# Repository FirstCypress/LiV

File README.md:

LiV is a sensor expansion board that turns your Raspberry Pi model B or B+ into a modern indoor air quality monitoring device that measures CO2, temperature, humidity and air pressure. 

LiV's software is released under a MIT license. 

LiV’s hardware is released under a cc-by-sa 4.0 license. 

LiV’s case is released under a cc-by-sa 4.0 license.

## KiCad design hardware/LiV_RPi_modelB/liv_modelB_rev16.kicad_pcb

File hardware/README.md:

LiV’s hardware is released under a cc-by-sa 4.0 license.

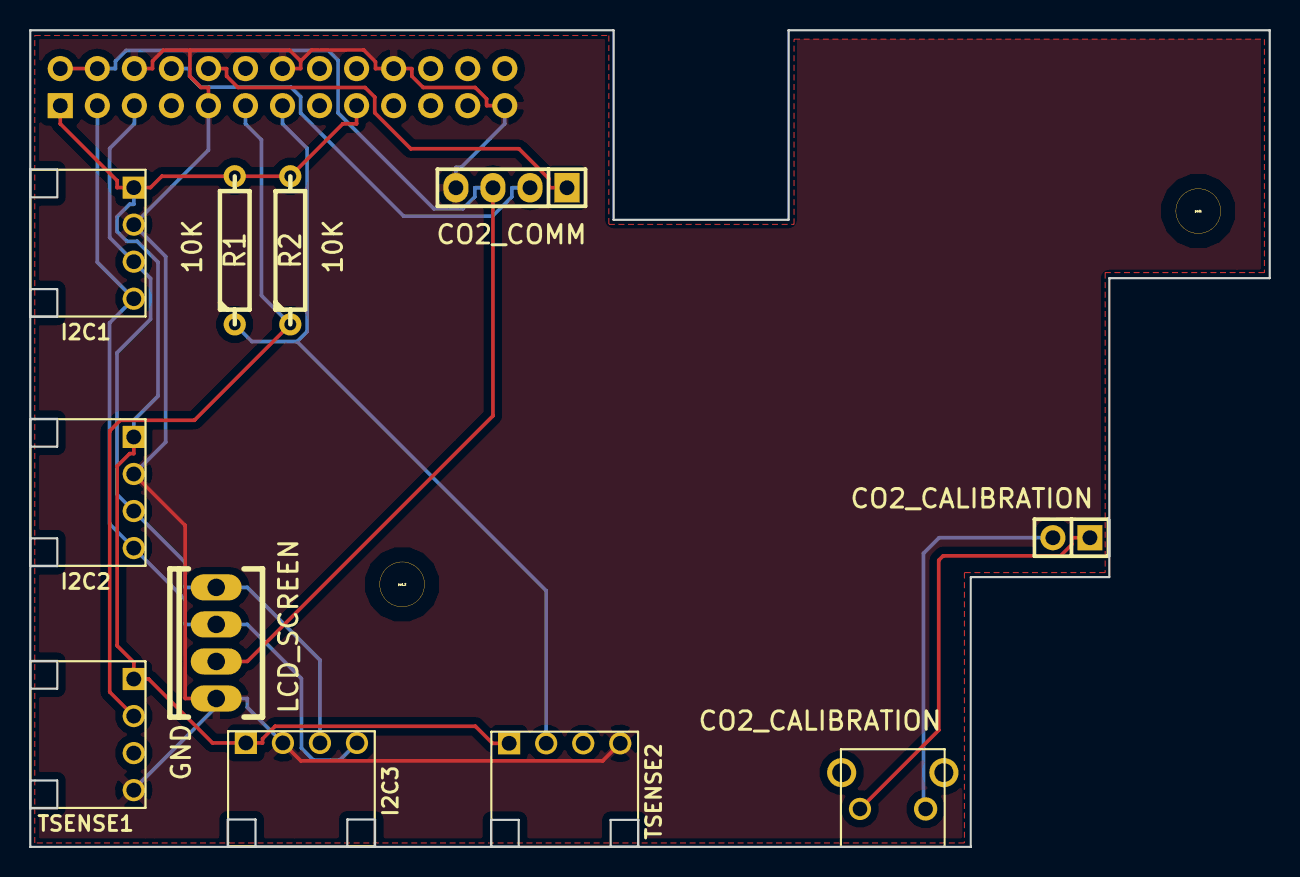
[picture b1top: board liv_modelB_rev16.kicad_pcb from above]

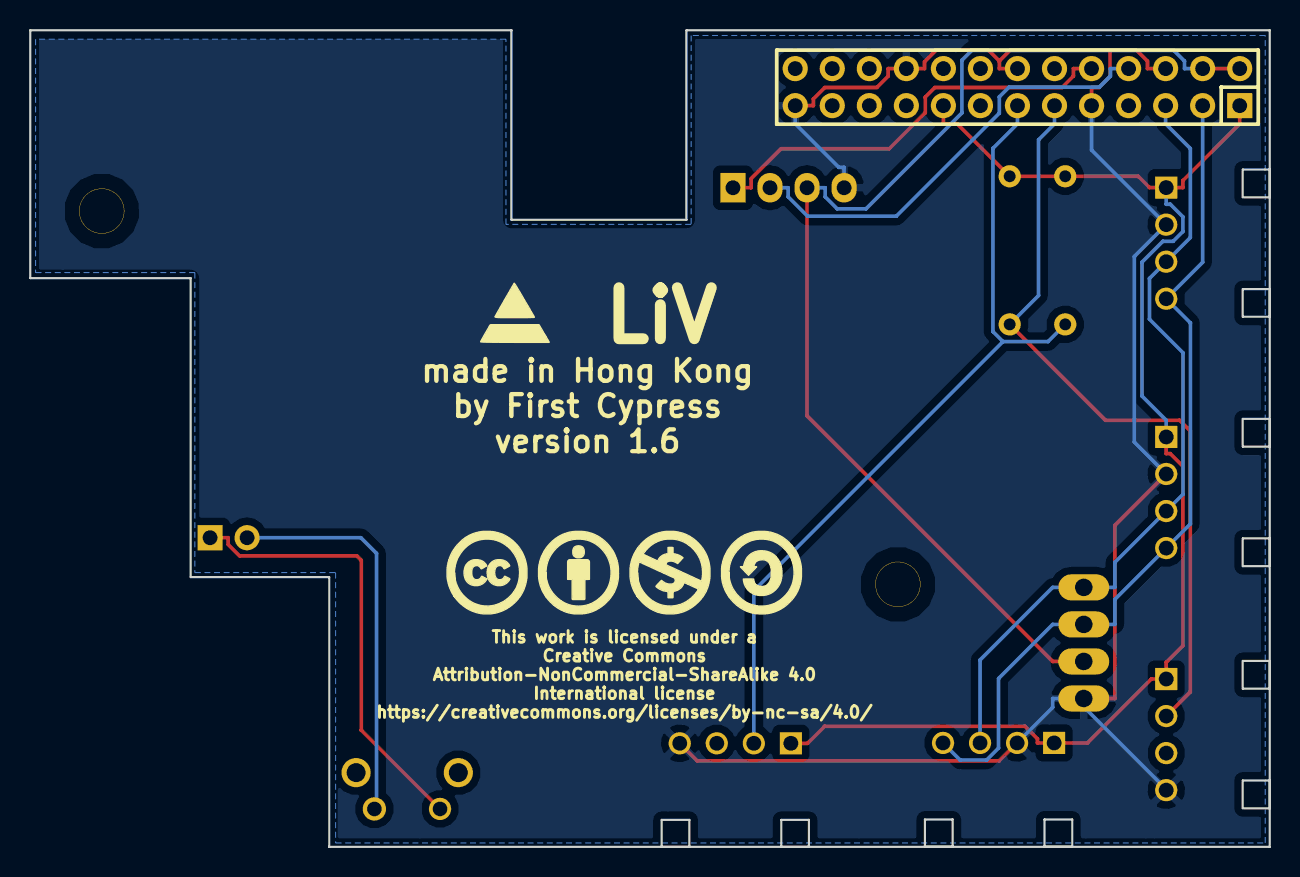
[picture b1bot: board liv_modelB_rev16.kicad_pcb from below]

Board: 2 copper layers, 85.0 x 56.0 mm, 15 parts (2 on the bottom side), 11 nets.

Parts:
P1: CONN_13X2; Socket_Strip_Straight_2x13
P3: LCD_SCREEN; Socket_MOLEX-KK-RM2-54mm_Lock_4pin_straight
P4: CO2_CALIBRATION; Socket_Strip_Straight_2x01
P5: CO2_COMM; Socket_Strip_Straight_1x04
P6: I2C1; CONNECTOR_MOLEX_4PIN_RIGHT_ANGLE
P7: I2C2; CONNECTOR_MOLEX_4PIN_RIGHT_ANGLE
P8: TSENSE2; CONNECTOR_MOLEX_4PIN_RIGHT_ANGLE
P9: TSENSE1; CONNECTOR_MOLEX_4PIN_RIGHT_ANGLE
P10: I2C3; CONNECTOR_MOLEX_4PIN_RIGHT_ANGLE
R1, R2: 10k; R4
SW1: CO2_CALIBRATION; SWITCH_TACT_RIGHT_ANGLE
cc_by_nc_sa_logo_only: LOGO; cc_by_nc_sa_logo_only
pad1: 1pin
pad_2: 1pin

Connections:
+3.3V: P1.1, P1.17, P6.1, P7.1, P8.1, P9.1, P10.1, R1.2, R2.2
+5V: P1.2, P1.4, P3.2, P5.3
/GPIO_2: P1.3, P3.3, P6.4, P7.4, P10.4
/GPIO_3: P1.5, P3.4, P6.3, P7.3, P10.3
/GPIO_14: P1.8, P5.2
/GPIO_15: P1.10, P5.1
/GPIO_17: P1.11, P9.2, R2.1
/GPIO_27: P1.13, P8.2, R1.1
GND: P1.6, P1.9, P1.14, P1.20, P1.25, P3.1, P5.4, P6.2, P7.2, P8.4, P9.4, P10.2
unnamed: P4.1, SW1.2
unnamed: P4.2, SW1.1

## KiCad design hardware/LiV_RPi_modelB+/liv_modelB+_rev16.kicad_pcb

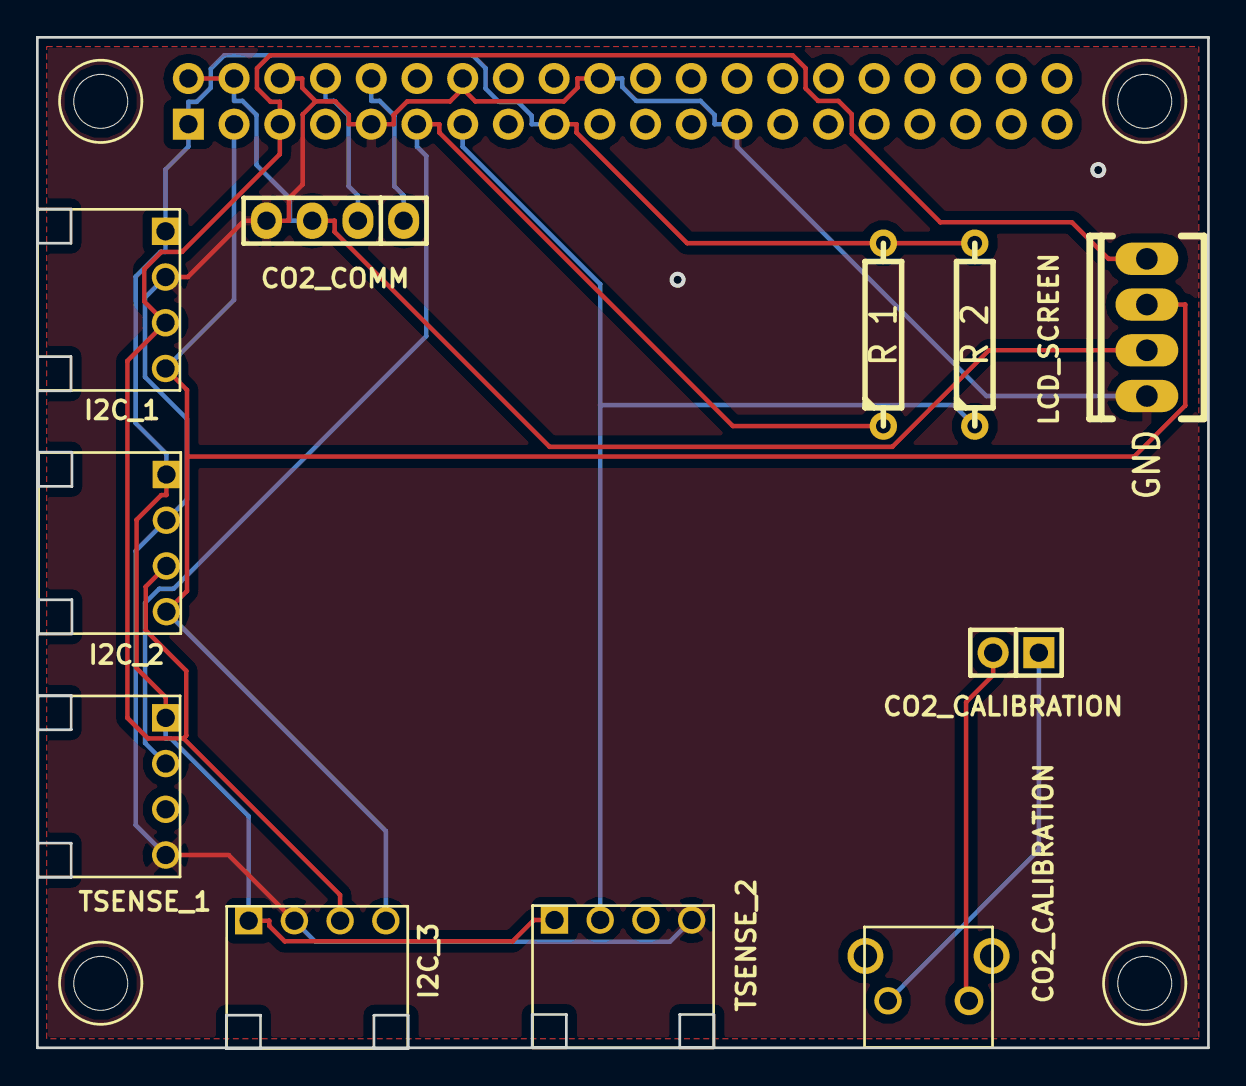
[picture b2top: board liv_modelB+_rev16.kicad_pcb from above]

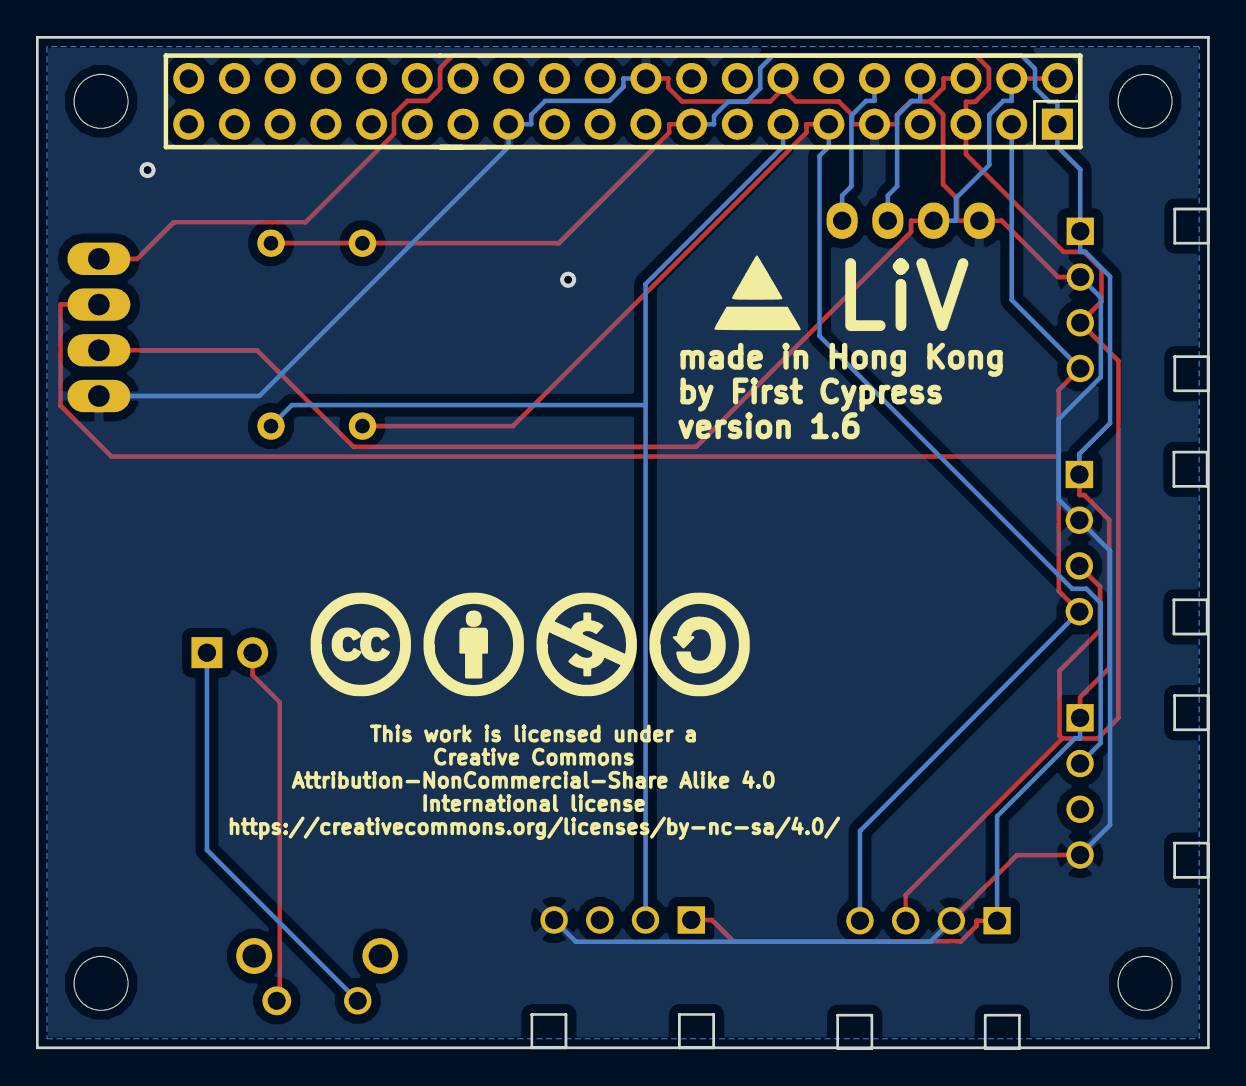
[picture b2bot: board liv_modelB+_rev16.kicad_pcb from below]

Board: 2 copper layers, 65.1 x 56.2 mm, 18 parts (3 on the bottom side), 11 nets.

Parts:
1_MNT_HOLE_RPI_PLUS, 2_MNT_HOLE_RPI_PLUS, 3_MNT_HOLE_RPI_PLUS, 4_MNT_HOLE_RPI_PLUS: mountingHole
R 1, R 2: 10k; R4
cc_by_nc_sa_logo_only: LOGO; cc_by_nc_sa_logo_only
co2_calibration1: CO2_CALIBRATION; SWITCH_TACT_RIGHT_ANGLE
co2_comm: CO2_COMM; Socket_Strip_Straight_1x04
co2_reset1: CO2_CALIBRATION; Socket_Strip_Straight_2x01
i2c_1: I2C_1; CONNECTOR_MOLEX_4PIN_RIGHT_ANGLE
i2c_2: I2C_2; CONNECTOR_MOLEX_4PIN_RIGHT_ANGLE
i2c_3: I2C_3; CONNECTOR_MOLEX_4PIN_RIGHT_ANGLE
liv_cone: LOGO; LivCypressOnlyLogo
rpi40: CONN_20X2; Socket_Strip_Straight_2x13
screen: LCD_SCREEN; Socket_MOLEX-KK-RM2-54mm_Lock_4pin_straight
temp_1: TSENSE_1; CONNECTOR_MOLEX_4PIN_RIGHT_ANGLE
temp_2: TSENSE_2; CONNECTOR_MOLEX_4PIN_RIGHT_ANGLE

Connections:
+3.3V: R 1.2, R 2.2, i2c_1.1, i2c_2.1, i2c_3.1, rpi40.1, rpi40.17, temp_1.1, temp_2.1
+5V: co2_comm.3, rpi40.2, rpi40.4, screen.2
/GPIO_2: i2c_1.4, i2c_2.4, i2c_3.4, rpi40.3, screen.3
/GPIO_3: i2c_1.3, i2c_2.3, i2c_3.3, rpi40.5, screen.4
/GPIO_14: co2_comm.2, rpi40.8
/GPIO_15: co2_comm.1, rpi40.10
/GPIO_17: R 1.1, rpi40.11, temp_1.2
/GPIO_27: R 2.1, rpi40.13, temp_2.2
GND: co2_comm.4, i2c_1.2, i2c_2.2, i2c_3.2, rpi40.6, rpi40.9, rpi40.14, rpi40.20, rpi40.25, screen.1, temp_1.4, temp_2.4
unnamed: co2_calibration1.1, co2_reset1.2
unnamed: co2_calibration1.2, co2_reset1.1

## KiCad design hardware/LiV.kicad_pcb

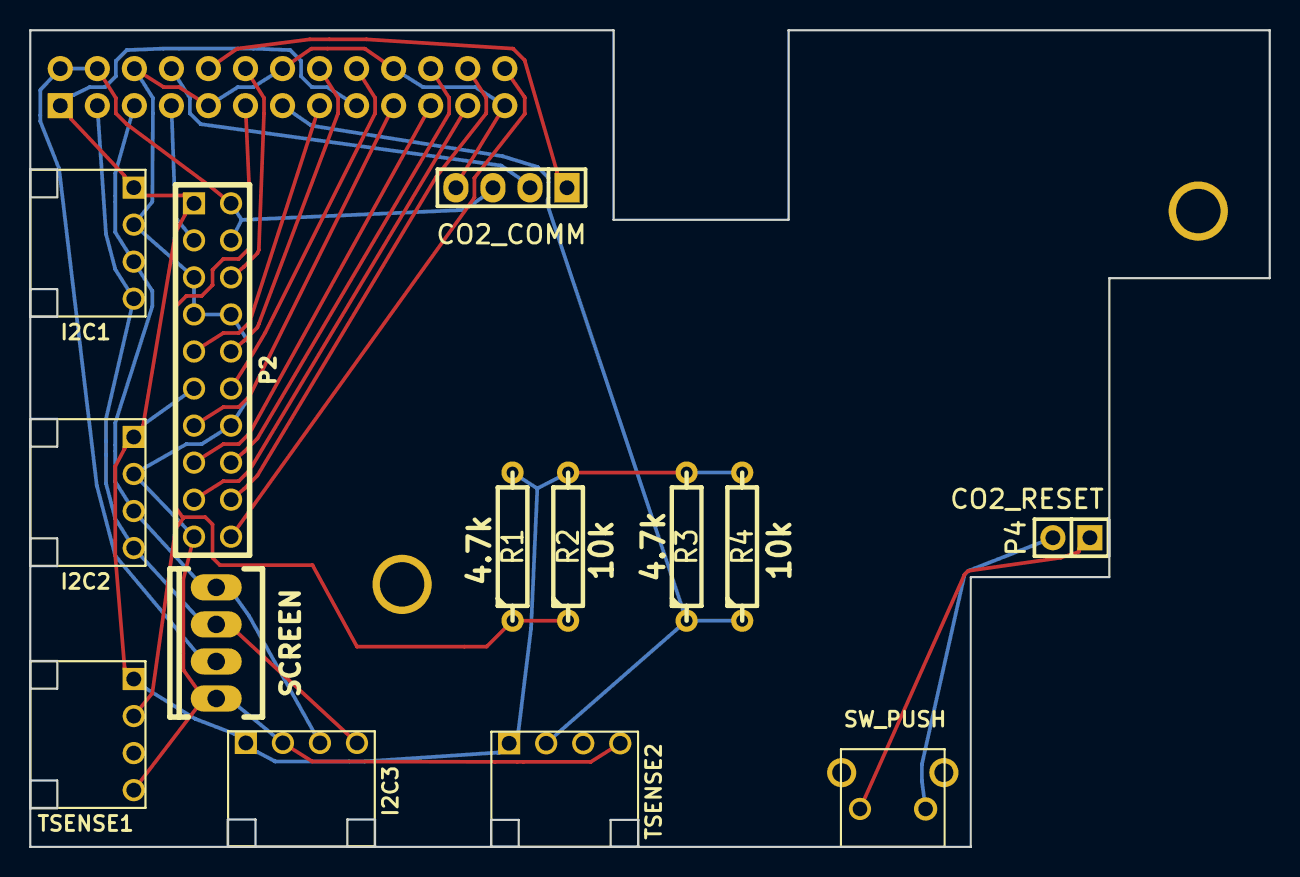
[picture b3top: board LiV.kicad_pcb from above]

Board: 2 copper layers, 85.0 x 56.0 mm, 15 parts (1 on the bottom side), 22 nets.

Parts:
P1: CONN_13X2; Socket_Strip_Straight_2x13
P2: CONN_10X2; pin_array_10x2
P3: SCREEN; Socket_MOLEX-KK-RM2-54mm_Lock_4pin_straight
P4: CO2_RESET; Socket_Strip_Straight_2x01
P5: CO2_COMM; Socket_Strip_Straight_1x04
P6: I2C1; CONNECTOR_MOLEX_4PIN_RIGHT_ANGLE
P7: I2C2; CONNECTOR_MOLEX_4PIN_RIGHT_ANGLE
P8: TSENSE2; CONNECTOR_MOLEX_4PIN_RIGHT_ANGLE
P9: TSENSE1; CONNECTOR_MOLEX_4PIN_RIGHT_ANGLE
P10: I2C3; CONNECTOR_MOLEX_4PIN_RIGHT_ANGLE
R1, R3: 4.7k; R4
R2, R4: 10k; R4
SW1: SW_PUSH; SWITCH_TACT_RIGHT_ANGLE

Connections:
+3.3V: P1.1, P1.17, P2.1, P2.11, P6.1, P7.1, P8.1, P9.1, P10.1, R1.2, R2.2, R3.2, R4.2
+5V: P1.2, P1.4, P2.2, P2.4, P3.2, P5.3
/GPIO_2: P1.3, P3.3, P6.4, P7.4, P10.4
/GPIO_3: P1.5, P3.4, P6.3, P7.3, P10.3
/GPIO_4: P1.7, P2.3
/GPIO_7: P1.26, P2.20
/GPIO_8: P1.24, P2.18
/GPIO_9: P1.21, P2.15
/GPIO_10: P1.19, P2.13
/GPIO_11: P1.23, P2.17
/GPIO_14: P1.8, P5.2
/GPIO_15: P1.10, P5.1
/GPIO_17: P1.11, P9.2, R1.1, R2.1
/GPIO_18: P1.12, P2.6
/GPIO_22: P1.15, P2.9
/GPIO_23: P1.16, P2.10
/GPIO_24: P1.18, P2.12
/GPIO_25: P1.22, P2.16
/GPIO_27: P1.13, P8.2, R3.1, R4.1
GND: P1.6, P1.9, P1.14, P1.20, P1.25, P2.5, P2.7, P2.8, P2.14, P2.19, P3.1, P5.4, P6.2, P7.2, P8.4, P9.4, P10.2
unnamed: P4.1, SW1.2
unnamed: P4.2, SW1.1

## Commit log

2014-11-16 inital commit v1_00
2014-11-16 added case repository v1_00
2014-11-16 add hardware directory
2014-11-17 added BOM
2015-01-08 add STL files in the case directory
2015-01-08 clean up old STL files
2015-01-08 create new directory to organize code
2015-01-08 added files for modelB+
2015-01-22 added XMPP connectivity to liv
2015-01-22 added logs to livAPIs directory
2015-01-22 added units to measurement readings for getAllSensorData API
2015-01-27 added start script for XMPP service
2015-02-16 removed old Adafruit directory
2015-02-16 created version v1_01
2015-02-16 created v1_01
2015-02-16 update config file
2015-03-20 added experimental devicehive code
2015-03-20 add DATA PUSH comment
2015-05-07 clean up LCD code, restructure start up scripts
2015-05-07 v1_02
2015-07-08 fix submodule issue
2015-07-08 added cardboard case, clean up files
2015-07-08 clean up files
2015-07-08 file cleanup
2015-07-08 files cleanup
2015-07-09 added xively sample code
2015-07-27 added latest PCB files
2015-09-05 added data.sparkfun and analog.io IoT sample code
2015-09-10 added 10s delay before livLCD starts so livDB writes measuremets into DB
2015-09-10 wait 10 sec before starting livLCD so livDB can write first measurements into DB
2015-09-10 fix for livLCD crash without CO2 sensor onboard
2015-10-06 added directory iotConnectors
2015-10-06 removed directory experimental
2016-03-31 branch creation
2016-03-31 S_development branch creation
2016-03-31 LCD process: display software version, add Fahrenheit and inHg display settings
2016-03-31 LCD: add version, F display for temp, inHg for air pressure
2016-03-31 added cleanLiVDB script
2016-04-01 small changes, cleanup
2016-04-01 cleanup
2016-04-03 replace twitter lib with tweepy
2016-04-05 rewrote temp and airpressure format handling
2016-09-01 added ifttt directory
2016-09-01 bug fix temp humidity
2017-06-01 remove Adafruit old Python libraries
2017-06-01 added README files
2017-12-08 added sonoff directory
2019-09-25 domoticz code
2019-09-25 added README
2024-04-11 Update license

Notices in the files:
hardware/LiV_RPi_modelB+/liv_modelB+_rev16.kicad_pcb:
This work is licensed under a
Creative Commons
Attribution-NonCommercial-Share Alike 4.0
https://creativecommons.org/licenses/by-nc-sa/4.0
